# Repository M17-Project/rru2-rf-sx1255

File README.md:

# RRU2 RF SX1255

This is an M.2 RF card for the M17 Remote Radio Unit v2 (RRU v2). The card
has the Semtech SX1255 transceiver for the 400 MHz to 510 MHz band. You can
replace the card with a card for a different band or a different chip. The
mainboard with the Raspberry Pi CM4 or CM5 stays the same. You can also use
the card without the RRU.

Revision A.

## Status

Work in progress. Not tested. Do not order.

## Block diagram

This diagram is preliminary. It can change.

```mermaid
flowchart LR
    M2["M.2 key E edge connector<br/>3.3 V, SPI with chip selects, I2S,<br/>I2C for control, ID_SD/ID_SC,<br/>GPIO, 10 MHz reference, PPS"]

    EEPROM["ID EEPROM<br/>Raspberry Pi HAT format"]
    PLL["ADF4002 PLL"]
    TCXO["32 MHz VCTCXO"]
    SX["SX1255 transceiver"]
    AMP["HMC374 amplifier"]
    ATT["3x PE4312<br/>digital step attenuator"]
    TXC["U.FL TX"]
    RXC["U.FL RX"]

    M2 -- "ID_SD, ID_SC" --> EEPROM
    M2 -- "SPI" --> SX
    M2 -- "SPI" --> ATT
    M2 <-->|"I2S"| SX

    M2 -- "10 MHz" --> PLL
    PLL -- "tune" --> TCXO
    TCXO -- "32 MHz" --> PLL
    TCXO -- "32 MHz" --> SX

    SX -- "TX" --> AMP
    AMP --> TXC

    RXC --> ATT
    ATT -- "RX" --> SX
```

The card has no other RF connectors. The M.2 connector has only power and
digital signals. The RF signals go through the two U.FL connectors.

## Key facts

| Item | Value |
|---|---|
| Form factor | M.2 key E, size 2230 or 2242 (not decided) |
| Board | 0.8 mm, 4 layers, JLCPCB stackup JLC04081H-7628 |
| RF connectors | 2x U.FL (TX and RX) |
| Frequency range | 400 MHz to 510 MHz (SX1255) |
| Output power | 22 dBm (P1dB) |

## Repository

This is a KiCad 10 project. The KiCad library is the git submodule `lib`. It is
the [M17 KiCad library](https://github.com/M17-Project/M17_kicad_library).
The [library README](https://github.com/M17-Project/M17_kicad_library#readme)
tells how to add parts.

### Get the files

Clone the repository with the library submodule:

```sh
git clone --recursive https://github.com/M17-Project/rru2-rf-sx1255.git
```

If you cloned without `--recursive`, get the library:

```sh
git submodule update --init
```

### Build

Install KiCad 10 and KiKit. Then run:

```sh
make
```

The build checks the design first. Any ERC or DRC violation stops the build.
Each part on the BOM must have a Mouser number or a source. The outputs are in `build/`.

To use the same tools as the CI, run the build in Docker:

```sh
make docker
```

To run only the checks, run:

```sh
make check
```

This target runs the ERC, the DRC with the schematic parity check, and the BOM
check. Any violation is an error.

### Update the library

```sh
make lib-update
```

Then open the project in KiCad and update the symbols and footprints.
Commit the `lib` submodule change together with the design change.

## License

This work is licensed under a
[Creative Commons Attribution-NonCommercial-ShareAlike 4.0 International License][cc-by-nc-sa].
Refer to `LICENSE.txt`.

[![CC BY-NC-SA 4.0][cc-by-nc-sa-image]][cc-by-nc-sa]

[cc-by-nc-sa]: http://creativecommons.org/licenses/by-nc-sa/4.0/
[cc-by-nc-sa-image]: https://licensebuttons.net/l/by-nc-sa/4.0/88x31.png

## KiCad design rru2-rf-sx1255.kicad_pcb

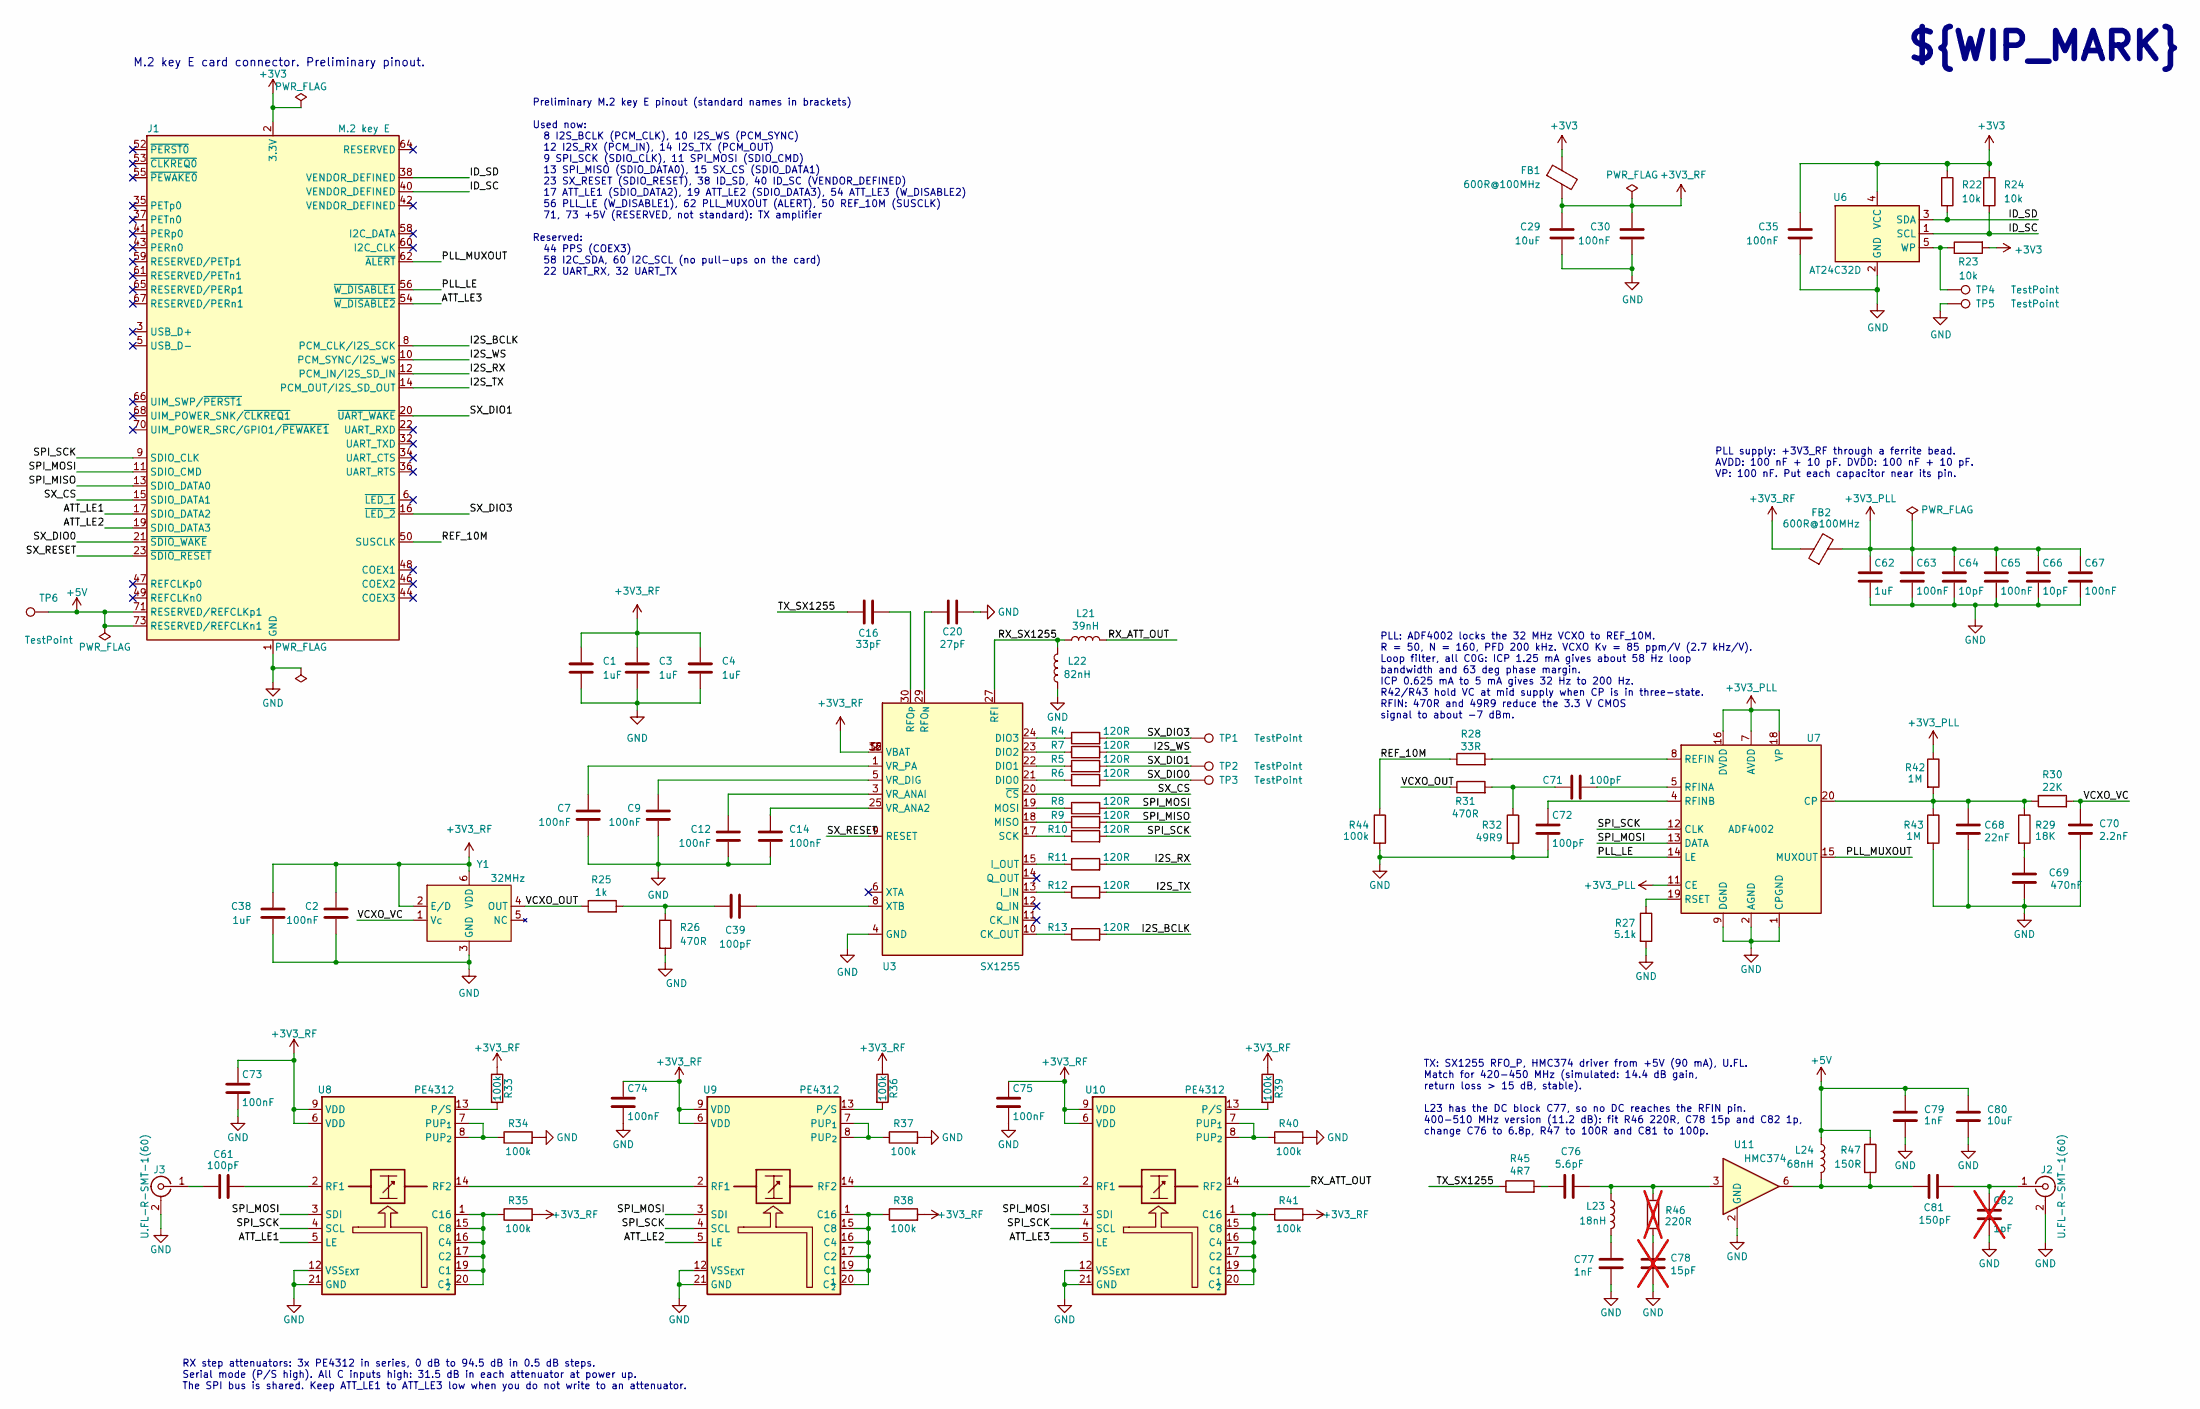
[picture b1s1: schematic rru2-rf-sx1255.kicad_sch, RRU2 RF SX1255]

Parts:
C1, C3, C4, C38, C62: 1uF; C_0402_1005Metric; Tolerance ±10%; Voltage 25V; MPN CL05A105KA5NQNC; Mouser 187-CL05A105KA5NQNC
C2, C7, C9, C12, C14, C30, C35, C63, C65, C67, C73, C74, C75: 100nF; C_0402_1005Metric; Tolerance ±10%; Voltage 50V; MPN CL05B104KB54PNC; Mouser 187-CL05B104KB54PNC
C16: 33pF; C_0402_1005Metric; Tolerance ±1%; Voltage 50V; MPN GJM1555C1H330FB01D; Mouser 81-GJM1555C1H330FB1D
C20: 27pF; C_0402_1005Metric; Tolerance ±1%; Voltage 50V; MPN GJM1555C1H270FB01D; Mouser 81-GJM1555C1H270FB1D
C29, C80: 10uF; C_0805_2012Metric; Tolerance ±10%; Voltage 25V; MPN CL21A106KAYNNNE; Mouser 187-CL21A106KAYNNNE
C39, C61, C71, C72: 100pF; C_0402_1005Metric; Tolerance ±5%; Voltage 50V; MPN GRM1555C1H101JA01D; Mouser 81-GRM1555C1H101JA1D
C64, C66: 10pF; C_0402_1005Metric; Tolerance ±1%; Voltage 50V; MPN GJM1555C1H100FB01D; Mouser 81-GJM1555C1H100FB01
C68: 22nF; C_0805_2012Metric; Tolerance ±5%; Voltage 50V; MPN GCM21B5C1H223JA16K; Mouser 81-GCM21B5C1H223JA6K
C69: 470nF; C_1206_3216Metric; Tolerance ±5%; Voltage 25V; MPN GRM31C5C1E474JE01L; Mouser 81-GRM31C5C1E474JE1L
C70: 2.2nF; C_0402_1005Metric; Tolerance ±5%; Voltage 50V; MPN GRM1555C1H222JA01D; Mouser 81-GRM1555C1H222J01D
C76: 5.6pF; C_0402_1005Metric; Tolerance ±0.1pF; Voltage 50V; MPN GJM1555C1H5R6BB01D; Mouser 81-GJM1555C1H5R6BB1D
C77, C79: 1nF; C_0402_1005Metric; Tolerance ±5%; Voltage 50V; MPN GRM1555C1H102JA01D; Mouser 81-GRM1555C1H102JA1D
C78: 15pF; C_0402_1005Metric; Tolerance ±2%; Voltage 50V; MPN GJM1555C1H150GB01D; Mouser 81-GJM1555C1H150GB01; not fitted
C81: 150pF; C_0402_1005Metric; Tolerance ±5%; Voltage 50V; MPN GCM1555C1H151JA16D; Mouser 81-GCM1555C1H151J16D
C82: 1pF; C_0402_1005Metric; Tolerance ±0.1pF; Voltage 50V; MPN GJM1555C1H1R0BB01D; Mouser 81-GJM1555C1H1R0BB01; not fitted
FB1, FB2: 600R@100MHz; L_0402_1005Metric; Tolerance ±25%; MPN BLM15PX601SN1D; Mouser 81-BLM15PX601SN1D
J1: M.2 key E; M.2_2242-xx-E
J2, J3: U.FL-R-SMT-1(60); U.FL_Hirose_U.FL-R-SMT-1_Vertical; MPN U.FL-R-SMT-1(60); Mouser 798-UFLRSMT160
L21: 39nH; L_0402_1005Metric; Tolerance ±2%; MPN LQW15AN39NG00D; Mouser 81-LQW15AN39NG00D
L22: 82nH; L_0402_1005Metric; Tolerance ±2%; MPN LQW15AN82NG00D; Mouser 81-LQW15AN82NG00D
L23: 18nH; L_0402_1005Metric; Tolerance ±2%; MPN LQW15AN18NG00D; Mouser 81-LQW15AN18NG00D
L24: 68nH; L_0402_1005Metric; Tolerance ±2%; MPN LQW15AN68NG00D; Mouser 81-LQW15AN68NG00D
R4, R5, R6, R7, R8, R9, R10, R11, R12, R13: 120R; R_0402_1005Metric; Tolerance ±1%; Voltage 50V; MPN 0402WGF1200TCE; Mouser 303-0402WGF1200TCE
R22, R23, R24: 10k; R_0402_1005Metric; Tolerance ±1%; Voltage 50V; MPN 0402WGF1002TCE; Mouser 303-0402WGF1002TCE
R25: 1k; R_0402_1005Metric; Tolerance ±1%; Voltage 50V; MPN 0402WGF1001TCE; Mouser 303-0402WGF1001TCE
R26, R31: 470R; R_0402_1005Metric; Tolerance ±1%; Voltage 50V; MPN 0402WGF4700TCE; Mouser 303-0402WGF4700TCE
R27: 5.1k; R_0402_1005Metric; Tolerance ±1%; Voltage 50V; MPN 0402WGF5101TCE; Mouser 303-0402WGF5101TCE
R28: 33R; R_0402_1005Metric; Tolerance ±1%; Voltage 50V; MPN 0402WGF330JTCE; Mouser 303-0402WGF330JTCE
R29: 18K; R_0402_1005Metric; Tolerance ±1%; Voltage 50V; MPN 0402WGF1802TCE; Mouser 303-0402WGF1802TCE
R30: 22K; R_0402_1005Metric; Tolerance ±1%; Voltage 50V; MPN 0402WGF2202TCE; Mouser 303-0402WGF2202TCE
R32: 49R9; R_0402_1005Metric; Tolerance ±1%; Voltage 50V; MPN RC0402FR-1049R9L; Mouser 603-RC0402FR-1049R9L
R33, R34, R35, R36, R37, R38, R39, R40, R41, R44: 100k; R_0402_1005Metric; Tolerance ±1%; Voltage 50V; MPN 0402WGF1003TCE; Mouser 303-0402WGF1003TCE
R42, R43: 1M; R_0402_1005Metric; Tolerance ±1%; Voltage 50V; MPN 0402WGF1004TCE; Mouser 303-0402WGF1004TCE
R45: 4R7; R_0402_1005Metric; Tolerance ±1%; Voltage 50V; MPN 0402WGF470KTCE; Mouser 303-0402WGF470KTCE
R46: 220R; R_0402_1005Metric; Tolerance ±1%; Voltage 50V; MPN 0402WGF2200TCE; Mouser 303-0402WGF2200TCE; not fitted
R47: 150R; R_0402_1005Metric; Tolerance ±1%; Voltage 50V; MPN 0402WGF1500TCE; Mouser 303-0402WGF1500TCE
TP1, TP2, TP3, TP4, TP5, TP6: TestPoint; TestPoint_Pad_D1.0mm
U3: SX1255; QFN-32-1EP_5x5mm_P0.5mm_EP3.3x3.3mm_ThermalVias; Mouser Part Number 947-SX1255IWLTRT
U6: AT24C32D; SOT-23-5; MPN AT24C32D-STUM-T; Mouser 556-AT24C32D-STUM-T
U7: ADF4002; LFCSP-20-1EP_4x4mm_P0.5mm_EP2.1x2.1mm; MPN ADF4002BCPZ-RL7; Mouser 584-ADF4002BCPZ-R7
U8, U9, U10: PE4312; QFN-20-1EP_4x4mm_P0.5mm_EP2.5x2.5mm; MPN PE4312C-Z; Mouser 81-PE4312C-Z
U11: HMC374; SOT-23-6; MPN HMC374ETR; Mouser 584-HMC374ETR
Y1: 32MHz; Oscillator_SMD_IDT_JS6-6_5.0x3.2mm_P1.27mm; MPN XLH53V032.000000I; Mouser 972-XLH53V032000000I

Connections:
+3V3: C35.1, FB1.1, J1.2 (3.3V), J1.4 (3.3V), J1.72 (3.3V), J1.74 (3.3V), R22.1, R23.2, R24.1, U6.4 (VCC)
+3V3_PLL: C62.1, C63.1, C64.1, C65.1, C66.1, C67.1, FB2.2, R42.1, U7.6 (AVDD), U7.7 (AVDD), U7.11 (CE), U7.16 (DVDD), U7.17 (DVDD), U7.18 (VP)
+3V3_RF: C1.1, C2.1, C3.1, C4.1, C29.1, C30.1, C38.1, C73.1, C74.1, C75.1, FB1.2, FB2.1, R33.1, R35.2, R36.1, R38.2, R39.1, R41.2, U3.2 (VBAT), U3.16 (VBAT), U3.32 (VBAT), U8.6 (VDD), U8.9 (VDD), U9.6 (VDD), U9.9 (VDD), U10.6 (VDD), U10.9 (VDD), Y1.2 (E/D), Y1.6 (VDD)
+5V: C79.1, C80.1, J1.71 (RESERVED/REFCLKp1), J1.73 (RESERVED/REFCLKn1), L24.1, R47.1, TP6.1 (1_1)
/ATT_LE1: J1.17 (SDIO_DATA2), U8.5 (LE)
/ATT_LE2: J1.19 (SDIO_DATA3), U9.5 (LE)
/ATT_LE3: J1.54 (~W_DISABLE2), U10.5 (LE)
/I2S_BCLK: J1.8 (PCM_CLK/I2S_SCK), R13.2
/I2S_RX: J1.12 (PCM_IN/I2S_SD_IN), R11.2
/I2S_TX: J1.14 (PCM_OUT/I2S_SD_OUT), R12.2
/I2S_WS: J1.10 (PCM_SYNC/I2S_WS), R7.2
/ID_SC: J1.40 (VENDOR_DEFINED), R24.2, U6.1 (SCL)
/ID_SD: J1.38 (VENDOR_DEFINED), R22.2, U6.3 (SDA)
/PLL_LE: J1.56 (~W_DISABLE1), U7.14 (LE)
/PLL_MUXOUT: J1.62 (~ALERT), U7.15 (MUXOUT)
/REF_10M: J1.50 (SUSCLK), R28.1, R44.1
/RX_ATT_OUT: L21.1, U10.14 (RF2)
/RX_SX1255: L21.2, L22.1, U3.27 (RFI)
/SPI_MISO: J1.13 (SDIO_DATA0), R9.2
/SPI_MOSI: J1.11 (SDIO_CMD), R8.2, U7.13 (DATA), U8.3 (SDI), U9.3 (SDI), U10.3 (SDI)
/SPI_SCK: J1.9 (SDIO_CLK), R10.2, U7.12 (CLK), U8.4 (SCL), U9.4 (SCL), U10.4 (SCL)
/SX_CS: J1.15 (SDIO_DATA1), U3.20 (~CS)
/SX_DIO0: J1.21 (~SDIO_WAKE), R6.2, TP3.1 (1_1)
/SX_DIO1: J1.20 (~UART_WAKE), R5.2, TP2.1 (1_1)
/SX_DIO3: J1.16 (~LED_2), R4.2, TP1.1 (1_1)
/SX_RESET: J1.23 (~SDIO_RESET), U3.9 (RESET)
/TX_SX1255: C16.1, R45.1
/VCXO_OUT: R25.1, R31.1, Y1.4 (OUT)
/VCXO_VC: C70.1, R30.2, Y1.1 (Vc)
GND: C1.2, C2.2, C3.2, C4.2, C7.2, C9.2, C12.2, C14.2, C20.2, C29.2, C30.2, C35.2, C38.2, C62.2, C63.2, C64.2, C65.2, C66.2, C67.2, C68.2, C69.2, C70.2, C72.2, C73.2, C74.2, C75.2, C77.2, C78.2, C79.2, C80.2, C82.2, J1.1 (GND), J1.7 (GND), J1.18 (GND), J1.33 (GND), J1.39 (GND), J1.45 (GND), J1.51 (GND), J1.57 (GND), J1.63 (GND), J1.69 (GND), J1.75 (GND), J2.2 (Ext), J3.2 (Ext), L22.2, R26.2, R27.2, R32.2, R34.2, R37.2, R40.2, R43.2, R44.2, TP5.1 (1_1), U3.4 (GND), U3.7 (GND), U3.26 (GND), U3.28 (GND), U3.31 (GND), U3.33 (GND), U6.2 (GND), U7.1 (CPGND), U7.2 (AGND), U7.3 (AGND), U7.9 (DGND), U7.10 (DGND), U7.21 (AGND), U8.10 (GND), U8.11 (GND), U8.12 (VSS_{EXT}), U8.18 (GND), U8.21 (GND), U9.10 (GND), U9.11 (GND), U9.12 (VSS_{EXT}), U9.18 (GND), U9.21 (GND), U10.10 (GND), U10.11 (GND), U10.12 (VSS_{EXT}), U10.18 (GND), U10.21 (GND), U11.2 (GND), U11.5 (GND), Y1.3 (GND)
unnamed: C39.2, R25.2, R26.1
unnamed: C69.1, R29.2
unnamed: C71.1, R31.2, R32.1
unnamed: C76.1, R45.2
unnamed: C76.2, L23.1, R46.1, U11.3
unnamed: C77.1, L23.2
unnamed: C78.1, R46.2
unnamed: C81.1, L24.2, R47.2, U11.6
unnamed: C81.2, C82.1, J2.1 (In)
unnamed: C61.1, J3.1 (In)
unnamed: R13.1, U3.10 (CK_OUT)
unnamed: R6.1, U3.21 (DIO0)
unnamed: R5.1, U3.22 (DIO1)
unnamed: R7.1, U3.23 (DIO2)
unnamed: R4.1, U3.24 (DIO3)
unnamed: R12.1, U3.13 (I_IN)
unnamed: R11.1, U3.15 (I_OUT)
unnamed: R9.1, U3.18 (MISO)
unnamed: R8.1, U3.19 (MOSI)
unnamed: C20.1, U3.29 (RFO_{N})
unnamed: C16.2, U3.30 (RFO_{P})
unnamed: R10.1, U3.17 (SCK)
unnamed: C14.1, U3.25 (VR_ANA2)
unnamed: C12.1, U3.3 (VR_ANAI)
unnamed: C9.1, U3.5 (VR_DIG)
unnamed: C7.1, U3.1 (VR_PA)
unnamed: C39.1, U3.8 (XTB)
unnamed: R23.1, TP4.1 (1_1), U6.5 (WP)
unnamed: C68.1, R29.1, R30.1, R42.2, R43.1, U7.20 (CP)
unnamed: R28.2, U7.8 (REFIN)
unnamed: C71.2, U7.5 (RFINA)
unnamed: C72.1, U7.4 (RFINB)
unnamed: R27.1, U7.19 (RSET)
unnamed: R35.1, U8.1 (C16), U8.15 (C8), U8.16 (C4), U8.17 (C2), U8.19 (C1), U8.20 (C½)
unnamed: R34.1, U8.7 (PUP_{1}), U8.8 (PUP_{2})
unnamed: R33.2, U8.13 (P/S)
unnamed: C61.2, U8.2 (RF1)
unnamed: U8.14 (RF2), U9.2 (RF1)
unnamed: R38.1, U9.1 (C16), U9.15 (C8), U9.16 (C4), U9.17 (C2), U9.19 (C1), U9.20 (C½)
unnamed: R37.1, U9.7 (PUP_{1}), U9.8 (PUP_{2})
unnamed: R36.2, U9.13 (P/S)
unnamed: R41.1, U10.1 (C16), U10.15 (C8), U10.16 (C4), U10.17 (C2), U10.19 (C1), U10.20 (C½)
unnamed: R40.1, U10.7 (PUP_{1}), U10.8 (PUP_{2})
unnamed: R39.2, U10.13 (P/S)
unnamed: U9.14 (RF2), U10.2 (RF1)

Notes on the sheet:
PLL: ADF4002 locks the 32 MHz VCXO to REF_10M. R = 50, N = 160, PFD 200 kHz. VCXO Kv = 85 ppm/V (2.7 kHz/V). Loop filter, all C0G: ICP 1.25 mA gives about 58 Hz loop bandwidth and 63 deg phase margin. ICP 0.625 mA to 5 mA gives 32 Hz to 200 Hz. R42/R43 hold VC at mid supply when CP is in three-stat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
RX step attenuators: 3x PE4312 in series, 0 dB to 94.5 dB in 0.5 dB steps. Serial mode (P/S high). All C inputs high: 31.5 dB in each attenuator at power up. The SPI bus is shared. Keep ATT_LE1 to ATT_LE3 low when you do not write to an attenuator.
Preliminary M.2 key E pinout (standard names in brackets) Used now: 8 I2S_BCLK (PCM_CLK), 10 I2S_WS (PCM_SYNC) 12 I2S_RX (PCM_IN), 14 I2S_TX (PCM_OUT) 9 SPI_SCK (SDIO_CLK), 11 SPI_MOSI (SDIO_CMD) 13 SPI_MISO (SDIO_DATA0), 15 SX_CS (SDIO_DATA1) 23 SX_RESET (SDIO_RESET), 38 ID_SD, 40 ID_SC (VENDOR_DE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
M.2 key E card connector. Preliminary pinout.
TX: SX1255 RFO_P, HMC374 driver from +5V (90 mA), U.FL. Match for 420-450 MHz (simulated: 14.4 dB gain, return loss > 15 dB, stable). L23 has the DC block C77, so no DC reaches the RFIN pin. 400-510 MHz version (11.2 dB): fit R46 220R, C78 15p and C82 1p, change C76 to 6.8p, R47 to 100R and C81 to 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
${WIP_MARK}
PLL supply: +3V3_RF through a ferrite bead. AVDD: 100 nF + 10 pF. DVDD: 100 nF + 10 pF. VP: 100 nF. Put each capacitor near its pin.

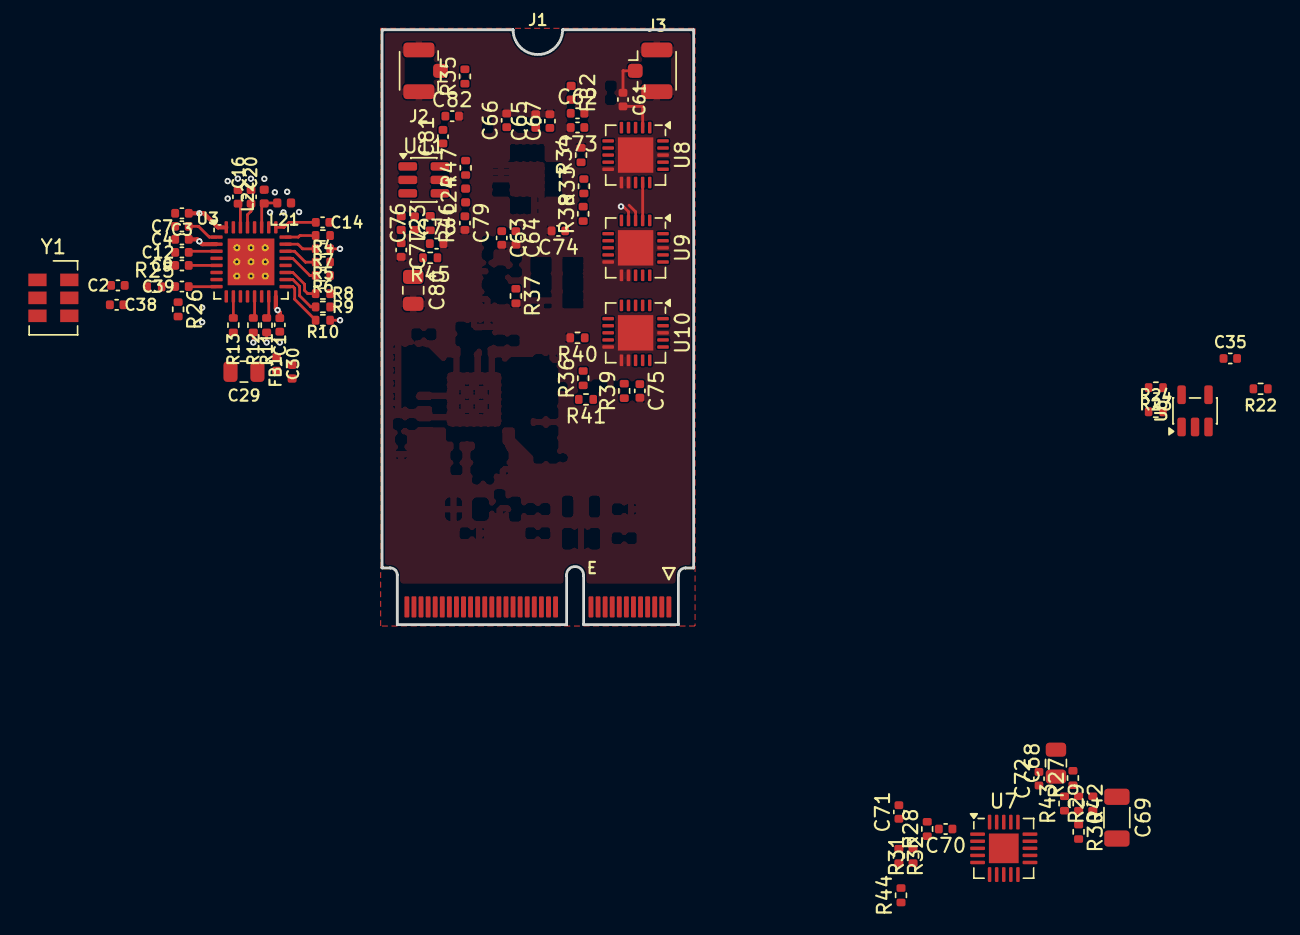
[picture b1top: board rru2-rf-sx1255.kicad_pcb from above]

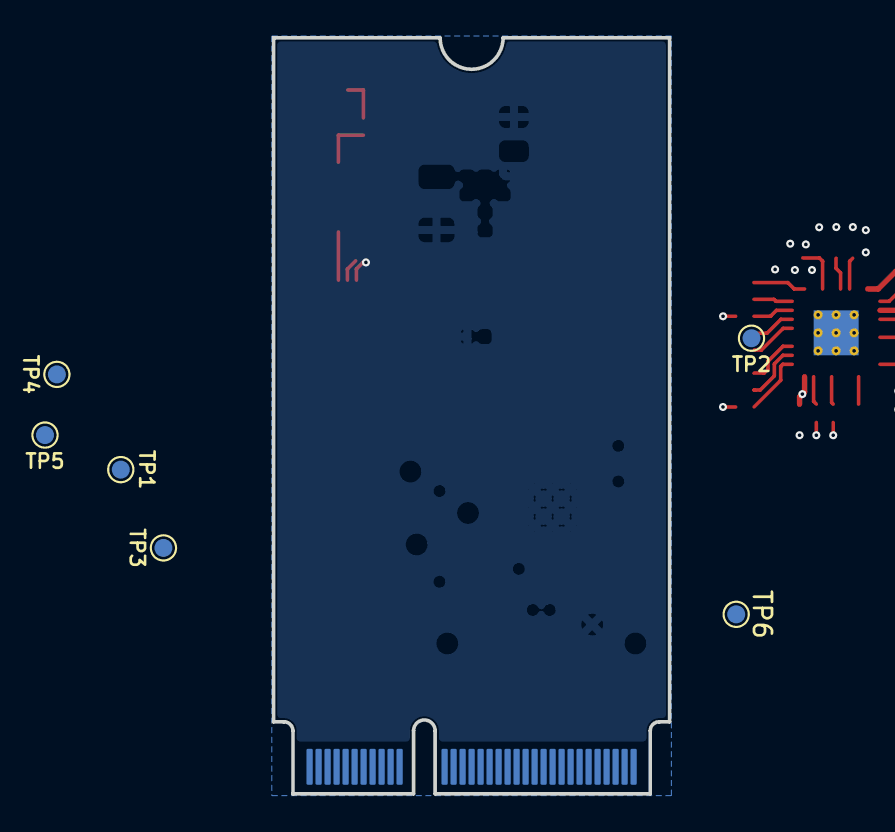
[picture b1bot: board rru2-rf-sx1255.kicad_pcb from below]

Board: 4 copper layers, 22.0 x 42.0 mm, 96 parts (6 on the bottom side), 75 nets.
